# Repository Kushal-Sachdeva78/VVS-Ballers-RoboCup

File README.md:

<h1 align="center">VVS Ballers: RoboCupJunior Soccer</h1>

<p align="center">
  Autonomous RoboCupJunior Soccer robots by Team VVS Ballers, designed and iterated
  across multiple seasons, from EV3 regional robots to a custom Teensy-based
  international platform.<br>
  Firmware (C++) · multi-board electronics (KiCad) · mechanical design (Fusion 360).<br>
  For RoboCupJunior teams building their own robots.
</p>

```bash
git clone https://github.com/Kushal-Sachdeva78/VVS-Ballers-RoboCup
```
<!-- DEMO: cut a 5-10 s GIF from "RoboCup Nationals 2025-26/Gallery/Finals Video.mp4", save as docs/demo.gif, then replace this line with  -->

---

## Results

- **RoboCup 2026, Incheon, South Korea (International): 9th place, RoboCupJunior Soccer (IR League).** Two self-built robots, designed, wired, and programmed by a team of two.
- **RoboCupJunior India, 2025-26 season**: came up through the Indian regional and national rounds to qualify for RoboCup 2026. The trophy and finals footage from the national event are in the [Nationals gallery](RoboCup%20Nationals%202025-26/Gallery).

## Press and media

- [Two Students, Two Self-Built Robots, And A 9th-Place Finish At The Robot "World Cup"](https://www.republicworld.com/sports/two-students-two-self-built-robots-and-a-ninth-place-finish-at-the-robot-world-cup-2026-07-14-132303) (Republic World, July 2026)
- [Team Instagram](https://www.instagram.com/vvs_ballers) - Robot builds, competition footage, and event coverage

---

## Seasons

| Season | What's inside |
|---|---|
| **[RoboCup Internationals 2025-26](RoboCup%20Internationals%202025-26/)** ⭐ *current* | Two autonomous Soccer-Infrared robots (attacker + defender): a Teensy 4.1 multi-board stack with an IR ball ring, line ring, ultrasonic, OpenMV goal camera, and 48 V solenoid kicker. Firmware + KiCad PCBs + Fusion CAD. |
| **[RoboCup Nationals 2025-26](RoboCup%20Nationals%202025-26/)** | Nationals build: EV3 robot program (HiTechnic IR seeker and compass), an Arduino relay-driven solenoid kicker, 3D-printed chassis parts, the season poster, and the trophy and finals gallery. |
| **[RoboCup Regionals 2025-26](RoboCup%20Regionals%202025-26/)** | EV3 holonomic robot (diamond omni drive, dual underside colour sensors, side IR distance, IR seeker, compass heading hold) + an Arduino ultrasonic-triggered kicker + printable parts + poster. |
| **[RoboCup 2024-25](RoboCup%202024-25/)** | Prior season: international Team Description Paper, posters, and earlier EV3 reference designs. |

> The **Internationals 2025-26** robots are the current flagship, and the rest of this
> page focuses on them. The full detail lives in that folder's
> **[detailed README](RoboCup%20Internationals%202025-26/README.md)** and a complete
> **[technical deep-dive](RoboCup%20Internationals%202025-26/Docs/HOW_IT_WORKS.md)**.
> Competition media: **[TDP](RoboCup%20Internationals%202025-26/Docs/TDP.md)** ·
> **[poster](RoboCup%20Internationals%202025-26/Docs/RoboCup_Internationals_Poster.png)** ·
> **[TDP video](https://github.com/Kushal-Sachdeva78/VVS-Ballers-RoboCup/releases/download/internationals-2025-26-media/VVS_Ballers_TDP_Video.mp4)** ·
> **[photo gallery](RoboCup%20Internationals%202025-26/Docs/Images)**.
>
> Code-span paths below (e.g. `Firmware/Attacker`) are relative to
> [`RoboCup Internationals 2025-26/`](RoboCup%20Internationals%202025-26/).

### Earlier-season highlights

- **Regionals 2025-26 (EV3):** EV3 motors driving omni wheels in a **diamond** layout;
  underside colour sensors for white-line and goal-area avoidance; side IR sensors for
  walls; an IR seeker for ball tracking; and a compass for heading correction. An
  external Arduino kicker (TB6612FNG H-bridge + gearmotor, ultrasonic ball detect)
  steps through kick, hold, retract, and cooldown phases.
- **Nationals 2025-26 (EV3):** the same EV3 sensing platform, upgraded with a
  relay-driven solenoid kicker triggered by an ultrasonic capture sensor. The custom
  Teensy and KiCad electronics stack was developed next, for the Internationals robots.

---

## Internationals 2025-26: the robots at a glance

Both robots share one electronics stack and one chassis; only the role firmware on
the main board differs.

| | Attacker | Defender (goalkeeper) |
|---|---|---|
| Job | Win the ball, aim, and shoot the open corner | Hold the goal mouth and clear the ball |
| Main firmware | `Firmware/Attacker/Attacker_Chase_Aim_Kick_Line` | `Firmware/Defender/Defender_Full` |
| Ball | IR ring (16 sensors) | IR ring |
| Staying in bounds | **Line ring + ultrasonic fused** boundary escape | **Line** keeps it on the goal-area ("D") line; ultrasonic cross-check |
| Goal / aim | OpenMV camera to open-corner bearing | (camera optional) |
| Kicker | 48 V solenoid, camera-gated | Short clearing kick |

## Electronics: the boards

A **multi-board design**: each subsystem has its own microcontroller, and the boards
talk to the main board over compact **UART links** (CRC-8-framed, bar the plain-ASCII
IR link), keeping the fast sensor loops off the main control CPU.

| Board | MCU | Does | KiCad | Firmware |
|---|---|---|---|---|
| **Main** | Teensy 4.1 | Drive (4x DRV8263H), BNO055 IMU, capture sensor, kicker relay, all links | `PCB/Main` | `Firmware/Attacker`, `Firmware/Defender` |
| **IR ring** | Teensy 4.1 | 16x TSSP58038 for ball bearing and distance | `PCB/IR` | `Firmware/IR_Ball_Sensor` |
| **Line ring** | Teensy 4.1 | 4x QTR-MD-05A (18 ch) for white-line detection | `PCB/Line` | `Firmware/Line_Sensor` |
| **Ultrasonic** | Arduino Nano Every | 4x HC-SR04 for wall distances | `PCB/Ultrasonic` | `Firmware/Ultrasonic` |
| **Camera** | OpenMV H7 | Goal / keeper / open-corner vision | - | `Firmware/Camera` |
| **Power** | - | 12 V / 5 V / 3.3 V rails + 48 V solenoid boost | `PCB/Power` | - |
| **Motor-current** (optional) | Arduino Nano Every | DRV8263H stall / over-current watchdog | - | `Firmware/Motor_Current` |

Human-readable wiring PDFs for the Main, Power, IR, and Line boards are in
**[`PCB/Wiring/`](RoboCup%20Internationals%202025-26/PCB/Wiring)**.

## How it plays: design choices vs. the game

Everything is built around what actually wins (and loses) a RoboCupJunior Soccer
match. (A goal counts when the ball touches the **back wall of the goal**; touching a
wall or driving fully into the marked penalty area is an **out-of-bounds penalty**.)

- **Score in the goal.** The IR ring gives the ball's bearing; the main board chases
  it with an omni-wheel drive held straight by a BNO055 heading PID. Once the ball is
  captured, the OpenMV camera finds the goal, picks the **open corner** (dodging the
  keeper), and the chassis turns in place until that corner is dead ahead before the
  solenoid fires. Aiming for the open corner instead of the goal centre is how you
  beat a keeper.

- **Never cross the line (the expensive mistake).** The attacker treats a side as the
  field boundary **only when the line ring and the ultrasonics agree** (white line
  seen *and* wall within 300 mm), then flees away from it. Two independent sensors
  must concur, so one noisy reading can't make the robot dart out of bounds.

- **Keep the keeper on its line, not inside the box.** No robot may be *fully* inside
  the penalty area, so the defender uses the line ring to ride the **edge of the goal
  area ("the D")** while tracking the ball laterally and clearing it on contact.

- **Stay legal in the Infrared league.** IR-emitting rangefinders (ToF, LiDAR, IR
  distance sensors) are **banned** because they'd swamp other robots' IR ball
  sensors. That is why walls are ranged with **ultrasonic** HC-SR04s here, not IR.

- **Power within the rules.** The rules cap robot power at **48 V DC**; the solenoid
  kicker runs from a 48 V boost converter (right at the legal ceiling, for the hardest
  legal kick) while logic and motors run from 3.3 V / 5 V / 12 V rails.

- **Referee start/stop.** The main board pins out the RoboCupJunior **Communication
  Module** GO/STOP inputs, with firmware support toggled via `USE_COMMS` in the
  defender build.

The binary inter-board links (ultrasonic, line, camera to main) are short frames, each
guarded by an identical **CRC-8 (poly 0x07)**; the IR link is plain delimited ASCII.
Full byte-level layouts are in the
[technical deep-dive](RoboCup%20Internationals%202025-26/Docs/HOW_IT_WORKS.md).

## Team

| Member | Roles |
|---|---|
| **Kushal Sachdeva** (Team Leader) | Electrical, Software & CAD |
| **Darsh Goel** | Mechanical & CAD |

Region: **India** · League: **RoboCupJunior Soccer Infrared**

## Sponsors

Our thanks to **Amazon · DLF · Havells · OpenMV · Magnum Ventures · Budtree
Management**, and to our mentors, school, and the RoboCup Junior community for their
support.

## Related projects

- [K.A.D-Ballers-Genius-Olympiad](https://github.com/Kushal-Sachdeva78/K.A.D-Ballers-Genius-Olympiad): our mecanum-drive robot for the GENIUS Olympiad robotics competition
- More at [github.com/Kushal-Sachdeva78](https://github.com/Kushal-Sachdeva78)

## License

Released under the **MIT License**; see [`LICENSE`](LICENSE).
© 2026 VVS Ballers (Kushal Sachdeva, Darsh Goel). You're welcome to learn from and
build on this work; please keep the attribution.

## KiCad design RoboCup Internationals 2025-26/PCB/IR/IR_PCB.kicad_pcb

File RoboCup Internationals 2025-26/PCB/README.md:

# PCB

KiCad sources, Gerbers, drill and job files for every board, plus human-readable
wiring and ready-to-order fab packages.

| Folder | Board | Contents |
|---|---|---|
| `Main/` | Main board (Teensy 4.1 carrier) | KiCad source + Gerbers — drivers, IMU, links, kicker relay (Main_PCB 2.0) |
| `IR/` | IR ball ring | 16× TSSP58038 + Teensy |
| `Line/` | Line ring | 4× QTR-MD-05A + Teensy |
| `Ultrasonic/` | Ultrasonic board | 4× HC-SR04 + Nano Every |
| `Power/` | Power board | 12 V / 5 V / 3.3 V rails + 48 V solenoid boost |
| `Wiring/` | — | **one wiring PDF per board** (the netlist in plain language) |
| `Fabrication/` | — | ready-to-order Gerber **zips** |

The previous main board revision is archived in
[`../Legacy/PCB/Main_v1`](../Legacy/PCB/Main_v1).

## Opening the sources

Each board folder is a KiCad project — open the `*.kicad_pro` (the matching
`.kicad_pcb` and `.kicad_sch` sit beside it). The loose `*.gbr` / `*.drl` /
`*.gbrjob` files are **generated** fabrication outputs; for ordering, prefer the
zipped packages in [`Fabrication/`](Fabrication). KiCad local-settings files
(`*.kicad_prl`) and auto-backups are intentionally git-ignored.

## Start with the wiring PDFs

If you only read one thing, read [`Wiring/`](Wiring): `Main_PCB.pdf`, `Power_PCB.pdf`,
`IR_PCB.pdf`, and `Line_PCB.pdf` list every connection (rails, sensor pins, UART
links) in plain language. They are the reference the firmware pin maps were verified
against.

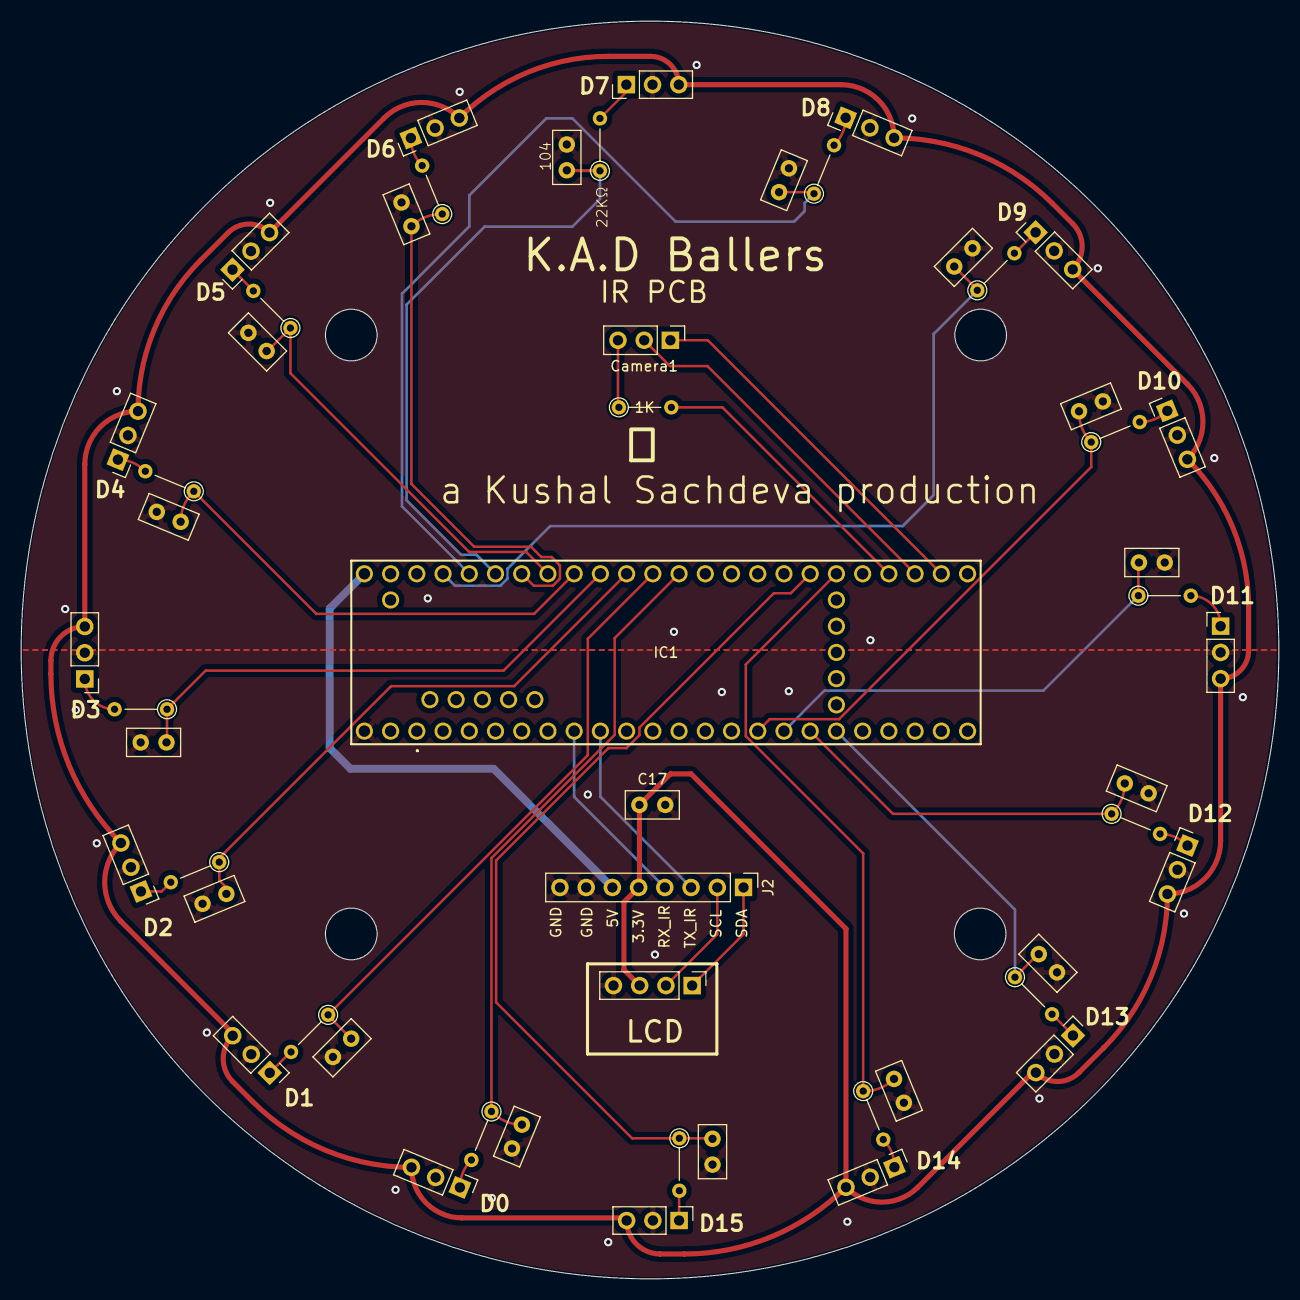
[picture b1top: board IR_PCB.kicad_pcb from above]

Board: 2 copper layers, 121.8 x 121.8 mm, 54 parts (0 on the bottom side), 43 nets.

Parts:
1K: 1K; R_Axial_DIN0204_L3.6mm_D1.6mm_P5.08mm_Vertical
C1, C2, C3, C4, C5, C6, C7, C8, C9, C10, C11, C12, C13, C14, C15, C16: 104; C_Disc_D5.0mm_W2.5mm_P2.50mm
C17: C; C_Disc_D5.0mm_W2.5mm_P2.50mm
Camera1: Conn_01x03; PinHeader_1x03_P2.54mm_Vertical
IC1: TEENSY_4.1; TEENSY41
J1: Conn_01x04_Socket; PinHeader_1x04_P2.54mm_Vertical
J2: Conn_01x08; PinHeader_1x08_P2.54mm_Vertical
R1, R2, R3, R4, R5, R6, R7, R8, R9, R10, R11, R12, R13, R14, R15, R16: 22k; R_Axial_DIN0204_L3.6mm_D1.6mm_P5.08mm_Vertical
U2, U3, U4, U5, U6, U7, U8, U9, U10, U11, U12, U13, U14, U15, U16, U17: TSSP58038; PinHeader_1x03_P2.54mm_Vertical

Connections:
+3.3V: C17.1, J1.3, J2.5, U2.3 (Vin), U3.3 (Vin), U4.3 (Vin), U5.3 (Vin), U6.3 (Vin), U7.3 (Vin), U8.3 (Vin), U9.3 (Vin), U10.3 (Vin), U11.3 (Vin), U12.3 (Vin), U13.3 (Vin), U14.3 (Vin), U15.3 (Vin), U16.3 (Vin), U17.3 (Vin)
+5V: IC1.55 (VIN_(3.6_TO_5.5_VOLTS)), J2.6
D0: C3.1, IC1.14 (A0), R3.1
D1: C4.1, IC1.15 (A1), R4.1
D2: C1.1, IC1.16 (A2), R1.1
D3: C2.1, IC1.17 (A3), R2.1
D4: C5.1, IC1.18 (A4), R5.1
D5: C6.1, IC1.19 (A5), R6.1
D6: C7.1, IC1.20 (A6), R7.1
D7: C8.1, IC1.21 (A7), R8.1
D8: C11.1, IC1.22 (A8), R11.1
D9: C12.1, IC1.23 (A9), R12.1
D10: C9.1, IC1.24 (A10), R9.1
D11: C10.1, IC1.25 (A11), R10.1
D12: C13.1, IC1.26 (A12), R13.1
D13: C14.1, IC1.27 (A13), R14.1
D14: C15.1, IC1.38 (A14), R15.1
D15: C16.1, IC1.39 (A15), R16.1
GND: C1.2, C2.2, C3.2, C4.2, C5.2, C6.2, C7.2, C8.2, C9.2, C10.2, C11.2, C12.2, C13.2, C14.2, C15.2, C16.2, C17.2, IC1.71 (GND_6), J1.4, J2.7, J2.8, U2.2 (GND), U3.2 (GND), U4.2 (GND), U5.2 (GND), U6.2 (GND), U7.2 (GND), U8.2 (GND), U9.2 (GND), U10.2 (GND), U11.2 (GND), U12.2 (GND), U13.2 (GND), U14.2 (GND), U15.2 (GND), U16.2 (GND), U17.2 (GND)
IRout0: R3.2, U2.1 (OUT)
IRout1: R4.2, U3.1 (OUT)
IRout2: R1.2, U4.1 (OUT)
IRout3: R2.2, U5.1 (OUT)
IRout4: R5.2, U6.1 (OUT)
IRout5: R6.2, U7.1 (OUT)
IRout6: R7.2, U8.1 (OUT)
IRout7: R8.2, U9.1 (OUT)
IRout8: R11.2, U10.1 (OUT)
IRout9: R12.2, U11.1 (OUT)
IRout10: R9.2, U12.1 (OUT)
IRout11: R10.2, U13.1 (OUT)
IRout12: R13.2, U14.1 (OUT)
IRout13: R14.2, U15.1 (OUT)
IRout14: R15.2, U16.1 (OUT)
IRout15: R16.2, U17.1 (OUT)
unnamed: 1K.1, Camera1.3
RST_C: 1K.2, IC1.36 (CS_2)
RX_Ball: IC1.7 (RX2), J2.4
RX_C: Camera1.2, IC1.35 (TX8)
SCL_LCD: J1.2, J2.2
SDA_LCD: J1.1, J2.1
TX_Ball: IC1.8 (TX2), J2.3
TX_C: Camera1.1, IC1.34 (RX8)

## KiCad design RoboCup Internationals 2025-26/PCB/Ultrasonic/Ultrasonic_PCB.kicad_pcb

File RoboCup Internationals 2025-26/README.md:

<h1 align="center">VVS Ballers — RoboCupJunior Soccer (Internationals 2025-26)</h1>

<p align="center">
  Two fully autonomous robots — an <b>attacker</b> and a <b>defender</b> — for the
  <b>RoboCupJunior Soccer Infrared</b> (formerly Lightweight) league.<br>
  Firmware(C++) · multi-board electronics (KiCad) · mechanical design (Fusion 360).
</p>

---

## About

This folder is the **Internationals 2025-26** season of the VVS Ballers
RoboCupJunior Soccer robots — the firmware that runs them, the PCBs that make up
their electronics, and the CAD for their chassis. The robots chase an infrared-emitting ball, find the goal with a
camera, kick with a solenoid, and stay inside the field using a line-sensor ring
backed up by ultrasonic ranging.

In **RoboCupJunior Soccer**, two teams of two robots play autonomous soccer on a
green field with white boundary lines. A goal is scored when the ball touches the
**back wall of the goal**; touching a wall or driving fully into the marked
penalty area is an **out-of-bounds penalty**. Every design decision here
is made against those facts — score in the goal, never cross the line, stay legal.
(See [How the robot works](Docs/HOW_IT_WORKS.md) for the full technical write-up.)

> **2026 ball note:** the Soccer Infrared league switched to the new 42 mm
> open-source [IR golf ball](https://github.com/robocup-junior/ir-golf-ball) — the
> same size as the Vision-league golf ball. The IR ring firmware here is tuned for it.

## Competition documents & media

| | |
|---|---|
| 📄 **Team Description Paper** | [`Docs/TDP.md`](Docs/TDP.md) |
| 🎬 **TDP video** | [Watch / download](https://github.com/Kushal-Sachdeva78/VVS-Ballers-RoboCup/releases/download/internationals-2025-26-media/VVS_Ballers_TDP_Video.mp4) (154 MB, hosted under [Releases](https://github.com/Kushal-Sachdeva78/VVS-Ballers-RoboCup/releases)) |
| 🖼️ **Poster** | [`Docs/RoboCup_Internationals_Poster.png`](Docs/RoboCup_Internationals_Poster.png) |
| 🎤 **Group-interview deck** | [`Docs/VVS_Ballers_GroupInterview_Deck.pptx`](Docs/VVS_Ballers_GroupInterview_Deck.pptx) |
| 📊 **Block diagram & BOM** | [`Docs/VVS_Ballers_Electronics_Block_Diagram.png`](Docs/VVS_Ballers_Electronics_Block_Diagram.png) · [`Docs/VVS_Ballers_BOM.xlsx`](Docs/VVS_Ballers_BOM.xlsx) |
| 📷 **Photo gallery** | [`Docs/Images/`](Docs/Images) — robots · electronics · mechanical · diagrams · team |

<p align="center">
  
</p>

## Team

| Member | Roles |
|---|---|
| **Kushal Sachdeva** (Team Leader) | Electrical, Software & CAD |
| **Darsh Goel** | Mechanical & CAD |

Region: **India** · League: **RoboCupJunior Soccer Infrared**

## The robots at a glance

Both robots share one electronics stack and one chassis; only the role firmware on
the main board differs.

| | Attacker | Defender (goalkeeper) |
|---|---|---|
| Job | Win the ball, aim, and shoot the open corner | Hold the goal mouth and clear the ball |
| Main firmware | `Firmware/Attacker/Attacker_Chase_Aim_Kick_Line` | `Firmware/Defender/Defender_Full` |
| Ball | IR ring (16 sensors) | IR ring |
| Staying in bounds | **Line ring + ultrasonic fused** boundary escape | **Line** keeps it on the goal-area ("D") line; ultrasonic cross-check |
| Goal / aim | OpenMV camera → open-corner bearing | (camera optional) |
| Kicker | 48 V solenoid, camera-gated | Short clearing kick |

## Electronics — the boards

The robot is a **multi-board design**: each subsystem has its own microcontroller,
and the boards talk to the main board over compact **UART links** (CRC-8-framed, bar
the plain-ASCII IR link). This keeps
the fast sensor loops off the main control CPU.

| Board | MCU | Does | KiCad | Firmware |
|---|---|---|---|---|
| **Main** | Teensy 4.1 | Drive (4× DRV8263H), BNO055 IMU, capture sensor, kicker relay, all links | `PCB/Main` | `Firmware/Attacker`, `Firmware/Defender` |
| **IR ring** | Teensy 4.1 | 16× TSSP58038 → ball bearing & distance | `PCB/IR` | `Firmware/IR_Ball_Sensor` |
| **Line ring** | Teensy 4.1 | 4× QTR-MD-05A (18 ch) → white-line detection | `PCB/Line` | `Firmware/Line_Sensor` |
| **Ultrasonic** | Arduino Nano Every | 4× HC-SR04 → wall distances | `PCB/Ultrasonic` | `Firmware/Ultrasonic` |
| **Camera** | OpenMV H7 | Goal / keeper / open-corner vision | — | `Firmware/Camera` |
| **Power** | — | 12 V / 5 V / 3.3 V rails + 48 V solenoid boost | `PCB/Power` | — |
| **Motor-current** (optional) | Arduino Nano Every | DRV8263H stall / over-current watchdog | — | `Firmware/Motor_Current` |

Wiring for every board is in **[`PCB/Wiring/`](PCB/Wiring)** (one PDF per board) and
explained in [How the robot works](Docs/HOW_IT_WORKS.md). A whole-robot
[electronics block diagram](Docs/VVS_Ballers_Electronics_Block_Diagram.png) and the
full [bill of materials](Docs/VVS_Ballers_BOM.xlsx) live in `Docs/`.

<p align="center"><i>The five boards — Main 2.0 · IR ring · Line ring · Power · Ultrasonic
(KiCad renders; build photos in <a href="Docs/Images/Electronics">Docs/Images/Electronics</a>)</i></p>

## How it plays — design choices vs. the game

Everything here is built around what actually wins (and loses) a RoboCupJunior
Soccer match:

- **Score in the goal.** The IR ring gives the ball's bearing; the main board chases
  it with an omni-wheel drive held straight by a BNO055 heading PID. Once the ball
  is captured, the OpenMV camera finds the goal, picks the **open corner** (dodging
  the keeper), and the chassis turns in place until that corner is dead ahead before
  the solenoid fires. Aiming the open corner instead of the goal centre is how you
  beat a keeper.

- **Never cross the line (the expensive mistake).** Touching a wall *or* driving
  fully into the marked penalty area is an **out-of-bounds penalty** — the robot is
  removed for a minute, and any goal scored while it's penalised is wiped. The
  attacker therefore treats a side as the field boundary **only when the line ring
  and the ultrasonics agree** (white line seen *and* wall within 300 mm), then flees
  away from it. Two independent sensors must concur, so one noisy reading can't make
  the robot dart out of bounds.

- **Keep the keeper on its line, not inside the box.** No robot may be *fully* inside
  the penalty area (that's out of bounds), so the defender uses the line ring to ride
  the **edge of the goal area ("the D")** — staying on the line rather than crossing
  it — while tracking the ball laterally and clearing it on contact.

- **Stay legal in the Infrared league.** IR-emitting rangefinders (ToF, LiDAR, IR
  distance sensors) are **banned** in the Infrared league because they'd swamp other
  robots' IR ball sensors — which is exactly why walls are ranged with **ultrasonic**
  HC-SR04s here, not IR. The reflectance line sensors face **down at the floor** and
  are shrouded so their light can't be mistaken for the orange ball by other teams'
  cameras.

- **Power within the rules.** The rules cap robot power at **48 V DC**; the solenoid
  kicker runs from a 48 V boost converter — right at the legal ceiling for the
  hardest legal kick — while logic and motors run from 3.3 V / 5 V / 12 V rails.

- **Referee start/stop.** The main board reads the RoboCupJunior **Communication
  Module** GO/STOP lines, so a referee can start and halt the robot as the rules
  require at the international competition.

## Folder structure

```
RoboCup Internationals 2025-26/
├─ README.md                  ← you are here
├─ Docs/
│  ├─ HOW_IT_WORKS.md         ← full technical deep-dive
│  ├─ MAPPING.md              ← original → new file/folder mapping
│  ├─ TDP.md                  ← Team Description Paper (Markdown)
│  ├─ TDP_images/             ← images embedded in TDP.md
│  ├─ RoboCup_Internationals_Poster.png
│  ├─ VVS_Ballers_GroupInterview_Deck.pptx
│  ├─ VVS_Ballers_BOM.xlsx    ← bill of materials
│  ├─ VVS_Ballers_Electronics_Block_Diagram.png
│  └─ Images/                 ← gallery: Robots · Electronics · Mechanical · Diagrams · Team
├─ Firmware/                  ← all microcontroller code
│  ├─ Attacker/               ← main-board attacker (current: …_Line)
│  ├─ Defender/               ← main-board goalkeeper (Defender_Full)
│  ├─ IR_Ball_Sensor/         ← IR ring (Code2_Calibrated = flight build)
│  ├─ Line_Sensor/            ← QTR line ring (Detect / Baseline / Raw)
│  ├─ Ultrasonic/             ← Nano Every HC-SR04 board + main-board parser
│  ├─ Camera/                 ← OpenMV H7 goal vision (MicroPython)
│  ├─ Motor_Current/          ← optional over-current watchdog
│  └─ README.md
├─ PCB/                       ← KiCad sources, Gerbers, wiring PDFs, fab zips
│  ├─ Main/ IR/ Line/ Ultrasonic/ Power/
│  ├─ Wiring/        ← human-readable wiring per board (PDF)
│  ├─ Fabrication/   ← ready-to-order Gerber zips
│  └─ README.md
├─ CAD/                       ← Fusion 360 sources + printable STLs
│  ├─ Fusion/   Printable/{Chassis, Drive, Ball_Capture, Sensor_Mounts}
│  └─ README.md
└─ Legacy/                    ← superseded designs, kept for history (see Legacy/README.md)
```

## Build & flash

All boards build in the **Arduino IDE** (each sketch folder is named to match its
`.ino`); the Teensy/Nano sketches also build under **PlatformIO** via the
`platformio.ini` in each folder.

| Target | Board setting | Libraries / notes |
|---|---|---|
| Main board (attacker/defender) | Teensy 4.1, USB Type *Serial* | Adafruit BNO055 + Adafruit Unified Sensor (Defender OLED option also needs SSD1306 + GFX) |
| IR ring | Teensy 4.1 | none (core `analogRead`) — flash `Code2_Calibrated` |
| Line ring | Teensy 4.1 | none |
| Ultrasonic | Arduino Nano Every (megaAVR) | none; *Registers emulation → None (ATMEGA4809)* |
| Motor-current | Arduino Nano Every | none |
| Camera | OpenMV H7 | save `Goal_Cam.py` to the H7 flash as `main.py` |

PlatformIO example: `pio run -e teensy41 -t upload` (Teensy) or
`pio run -e nano_every -t upload` (Nano).

## Inter-board links (summary)

Three of the four links are short binary frames with a 2-byte sync and an identical
**CRC-8 (poly 0x07)**, so the main board can reject any corrupted frame; the IR link
is plain delimited ASCII:

- **IR → Main** (Serial4): ASCII `"<dir>a … <dist>b"`, `500` = no ball (no checksum).
- **Ultrasonic → Main** (Serial3): 13-byte frame, four `uint16` mm distances + status.
- **Line → Main** (Serial8): 9-byte frame, per-side white-line bitmask + counts.
- **Camera → Main** (Serial2): 11-byte frame, goal/keeper/ball flags + bearings,
  open-corner angle, and the orange-ball bearing/distance (camera+IR fusion).

Full byte-level layouts are in [How the robot works](Docs/HOW_IT_WORKS.md).

## Sponsors

Our thanks to **Amazon · DLF · Havells · OpenMV · Magnum Ventures · Budtree
Management** for supporting the team.

## License

Released under the [MIT License](LICENSE) © 2026 VVS Ballers. You're welcome to
learn from and build on this work — please keep the attribution.

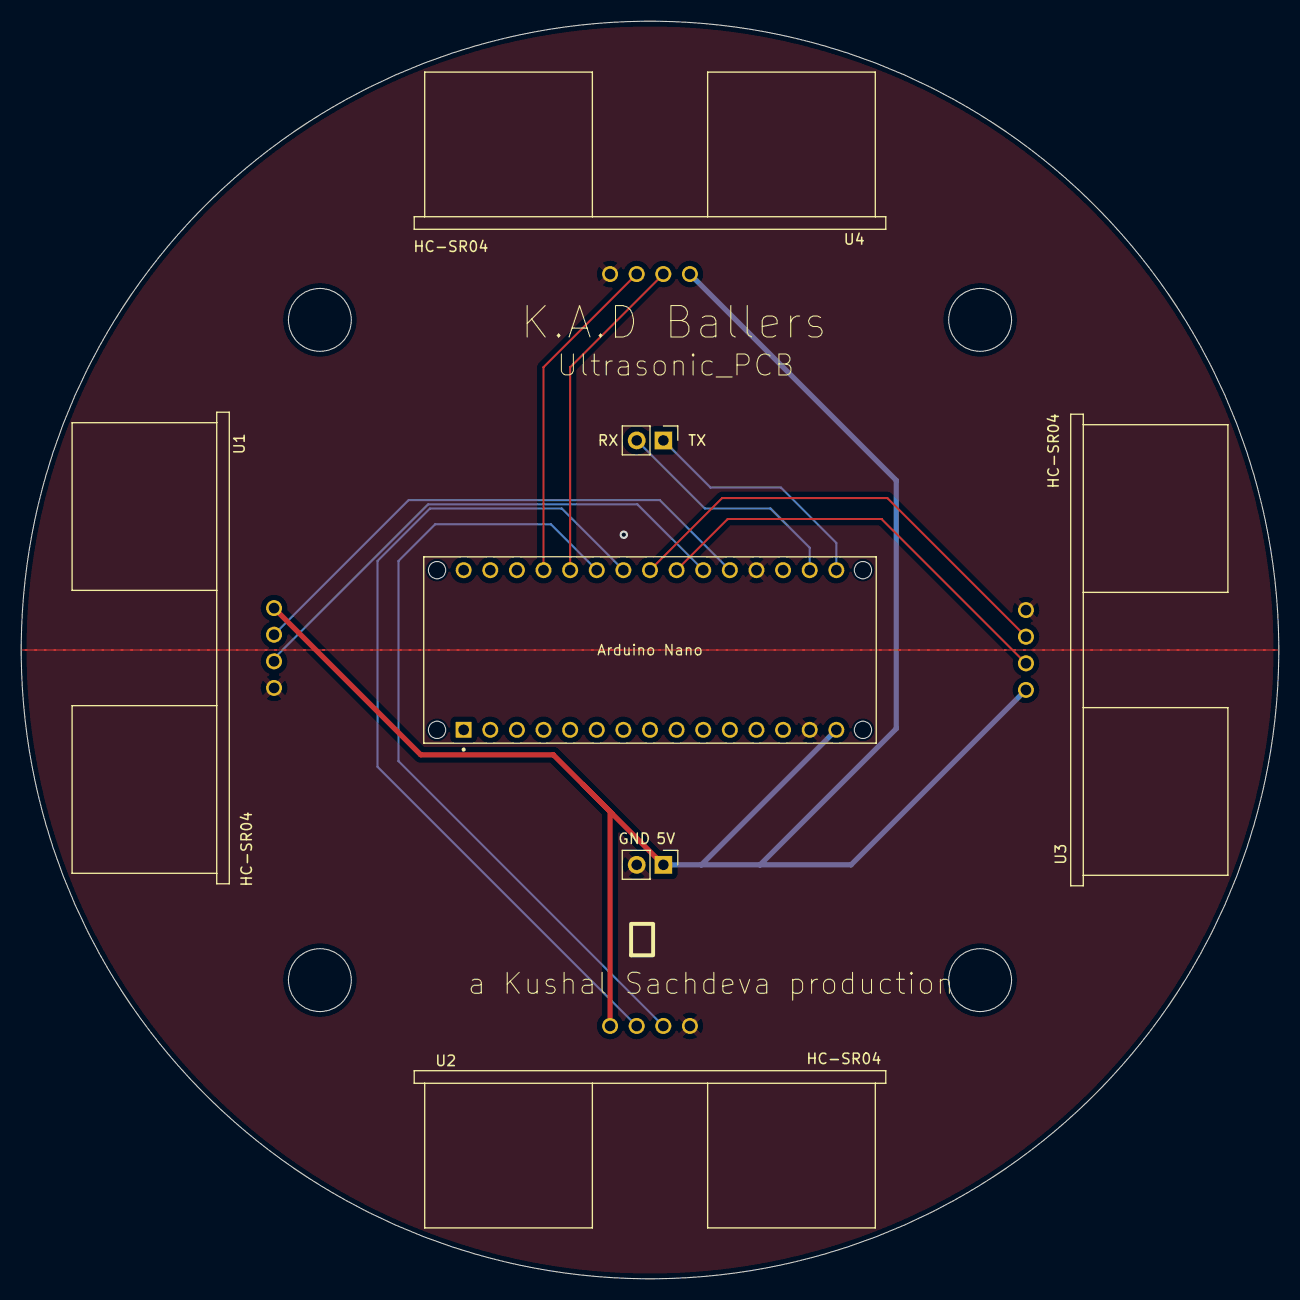
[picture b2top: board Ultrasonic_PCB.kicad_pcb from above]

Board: 2 copper layers, 120.0 x 120.0 mm, 7 parts (0 on the bottom side), 12 nets.

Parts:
5V: Conn_01x02; PinHeader_1x02_P2.54mm_Vertical
Arduino Nano: ABX00028; MODULE_ABX00028
RX: Conn_01x02; PinHeader_1x02_P2.54mm_Vertical
U1, U2, U3, U4: HC-SR04; XCVR_HC-SR04

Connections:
GND: 5V.2, Arduino Nano.14 (GND), Arduino Nano.19 (GND), U1.4 (GND), U2.4 (GND), U3.4 (GND), U4.4 (GND)
unnamed: 5V.1, Arduino Nano.15 (VIN), U1.1 (VCC), U2.1 (VCC), U3.1 (VCC), U4.1 (VCC)
unnamed: Arduino Nano.16 (TX), RX.1
unnamed: Arduino Nano.17 (RX), RX.2
unnamed: Arduino Nano.20 (D2), U1.2 (TRIG)
unnamed: Arduino Nano.21 (D3/PWM), U1.3 (ECHO)
unnamed: Arduino Nano.22 (D4), U3.2 (TRIG)
unnamed: Arduino Nano.23 (D5/PWM), U3.3 (ECHO)
unnamed: Arduino Nano.24 (D6/PWM), U2.2 (TRIG)
unnamed: Arduino Nano.25 (D7), U2.3 (ECHO)
unnamed: Arduino Nano.26 (D8), U4.2 (TRIG)
unnamed: Arduino Nano.27 (D9/PWM), U4.3 (ECHO)

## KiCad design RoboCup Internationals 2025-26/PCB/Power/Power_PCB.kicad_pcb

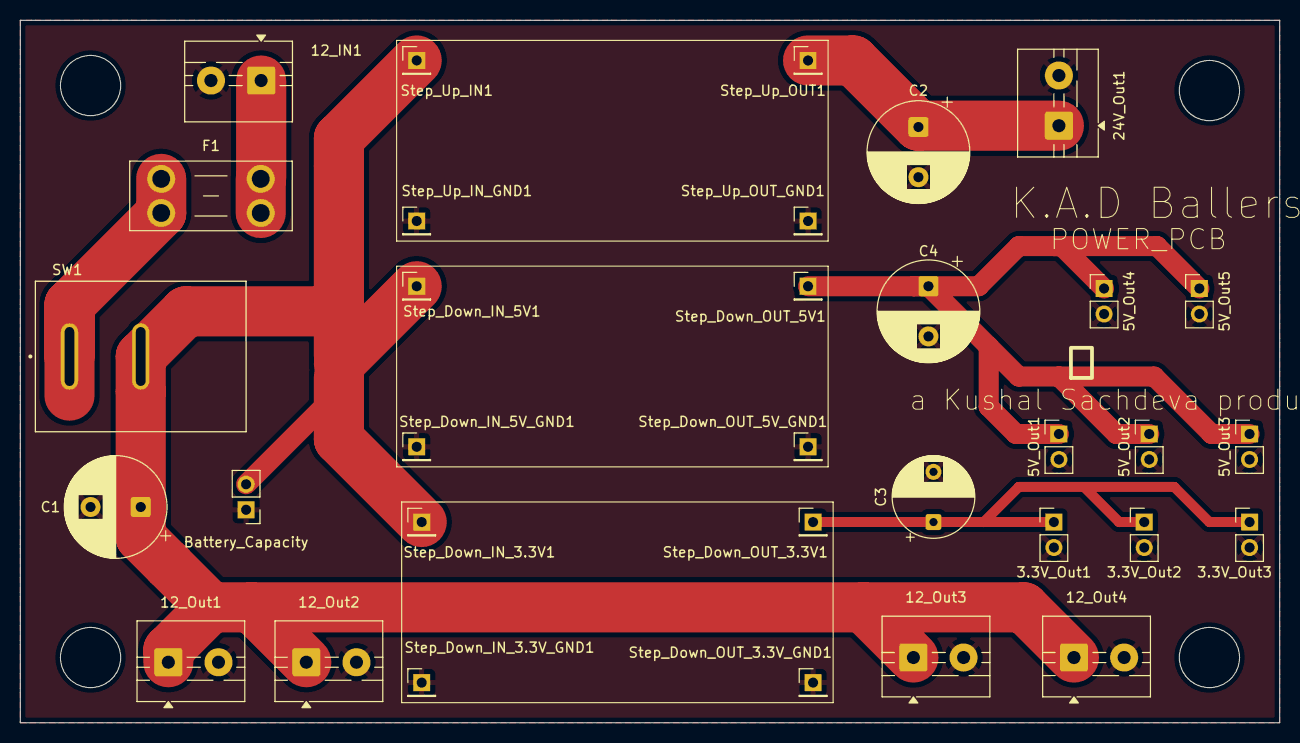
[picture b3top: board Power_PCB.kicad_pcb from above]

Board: 2 copper layers, 125.5 x 70.0 mm, 33 parts (0 on the bottom side), 7 nets.

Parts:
3.3V_Out1, 3.3V_Out2, 3.3V_Out3: Conn_01x02; PinHeader_1x02_P2.54mm_Vertical
5V_Out1: IR; PinHeader_1x02_P2.54mm_Vertical
5V_Out2: Line; PinHeader_1x02_P2.54mm_Vertical
5V_Out3: Main_PCB; PinHeader_1x02_P2.54mm_Vertical
5V_Out4: US_PCB; PinHeader_1x02_P2.54mm_Vertical
5V_Out5: Camera; PinHeader_1x02_P2.54mm_Vertical
12_IN1, 12_Out1, 12_Out2, 12_Out3, 12_Out4: Screw_Terminal_01x02; TerminalBlock_MaiXu_MX126-5.0-02P_1x02_P5.00mm
24V_Out1: Conn_01x02; TerminalBlock_MaiXu_MX126-5.0-02P_1x02_P5.00mm
Battery_Capacity: Conn_01x02; PinHeader_1x02_P2.54mm_Vertical
C1, C2, C4: C; CP_Radial_D10.0mm_P5.00mm
C3: C; CP_Radial_D8.0mm_P5.00mm
F1: Fuse; Fuseholder_Blade_Mini_Keystone_3568
SW1: SW_DIP_x01; SW_RF1-1A-DC-2-R-1
Step_Down_IN_3.3V1, Step_Down_IN_3.3V_GND1, Step_Down_IN_5V1, Step_Down_IN_5V_GND1: Conn_01x01; PinHeader_1x01_P2.54mm_Vertical
Step_Down_OUT_3.3V1, Step_Down_OUT_3.3V_GND1, Step_Down_OUT_5V1, Step_Down_OUT_5V_GND1: Conn_01x01; PinHeader_1x01_P2.54mm_Vertical
Step_Up_IN1: Conn_01x01; PinHeader_1x01_P2.54mm_Vertical
Step_Up_IN_GND1: Conn_01x01; PinHeader_1x01_P2.54mm_Vertical
Step_Up_OUT1: Conn_01x01; PinHeader_1x01_P2.54mm_Vertical
Step_Up_OUT_GND1: Conn_01x01; PinHeader_1x01_P2.54mm_Vertical

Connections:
GND: 3.3V_Out1.2, 3.3V_Out2.2, 3.3V_Out3.2, 5V_Out1.2, 5V_Out2.2, 5V_Out3.2, 5V_Out4.2, 5V_Out5.2, 12_IN1.2, 12_Out1.2, 12_Out2.2, 12_Out3.2, 12_Out4.2, 24V_Out1.2, Battery_Capacity.1, C1.2, C2.2, C3.2, C4.2, Step_Down_IN_3.3V_GND1.1, Step_Down_IN_5V_GND1.1, Step_Down_OUT_3.3V_GND1.1, Step_Down_OUT_5V_GND1.1, Step_Up_IN_GND1.1, Step_Up_OUT_GND1.1
unnamed: 3.3V_Out1.1, 3.3V_Out2.1, 3.3V_Out3.1, C3.1, Step_Down_OUT_3.3V1.1
unnamed: 5V_Out1.1, 5V_Out2.1, 5V_Out3.1, 5V_Out4.1, 5V_Out5.1, C4.1, Step_Down_OUT_5V1.1
unnamed: 12_IN1.1, F1.2
unnamed: 12_Out1.1, 12_Out2.1, 12_Out3.1, 12_Out4.1, Battery_Capacity.2, C1.1, SW1.2, Step_Down_IN_3.3V1.1, Step_Down_IN_5V1.1, Step_Up_IN1.1
unnamed: 24V_Out1.1, C2.1, Step_Up_OUT1.1
unnamed: F1.1, SW1.1

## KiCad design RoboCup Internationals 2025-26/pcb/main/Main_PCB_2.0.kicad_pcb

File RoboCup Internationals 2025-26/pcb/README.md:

# PCB

KiCad sources, Gerbers, drill and job files for every board, plus human-readable
wiring and ready-to-order fab packages.

| Folder | Board | Contents |
|---|---|---|
| `main/` | Main board (Teensy 4.1 carrier) | KiCad source + Gerbers — drivers, IMU, links, kicker relay (Main_PCB 2.0) |
| `ir/` | IR ball ring | 16× TSSP58038 + Teensy |
| `line/` | Line ring | 4× QTR-MD-05A + Teensy |
| `ultrasonic/` | Ultrasonic board | 4× HC-SR04 + Nano Every |
| `power/` | Power board | 12 V / 5 V / 3.3 V rails + 48 V solenoid boost |
| `wiring/` | — | **one wiring PDF per board** (the netlist in plain language) |
| `fab/` | — | ready-to-order Gerber **zips** |

The previous main board revision is archived in
[`../legacy/pcb/main-v1`](../legacy/pcb/main-v1).

## Opening the sources

Each board folder is a KiCad project — open the `*.kicad_pro` (the matching
`.kicad_pcb` and `.kicad_sch` sit beside it). The loose `*.gbr` / `*.drl` /
`*.gbrjob` files are **generated** fabrication outputs; for ordering, prefer the
zipped packages in [`fab/`](fab). KiCad local-settings files (`*.kicad_prl`) and
auto-backups are intentionally git-ignored.

## Start with the wiring PDFs

If you only read one thing, read [`wiring/`](wiring): `Main_PCB.pdf`, `Power_PCB.pdf`,
`IR_PCB.pdf`, and `Line_PCB.pdf` list every connection (rails, sensor pins, UART
links) in plain language. They are the reference the firmware pin maps were verified
against.

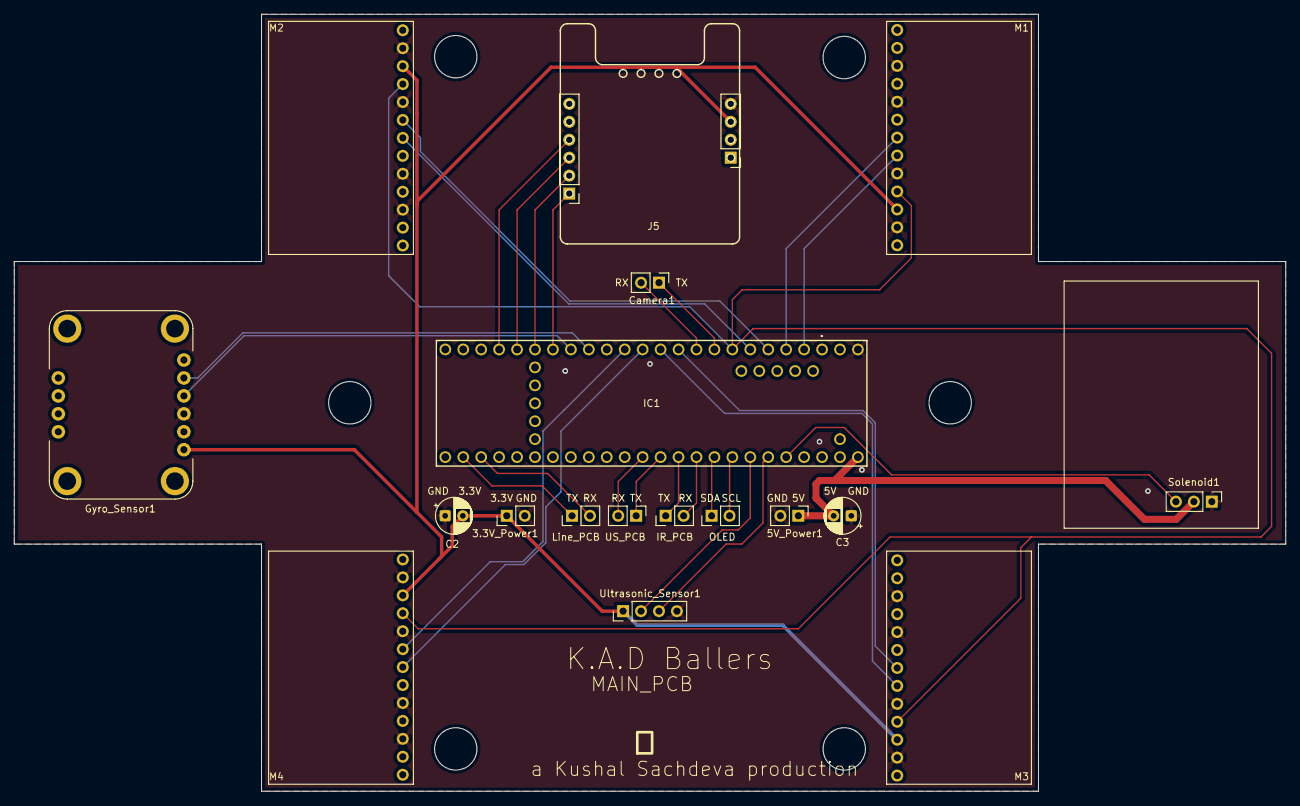
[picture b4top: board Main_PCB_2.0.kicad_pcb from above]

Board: 2 copper layers, 180.0 x 110.0 mm, 19 parts (0 on the bottom side), 31 nets.

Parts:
3.3V_Power1, 5V_Power1: Conn_01x02; PinHeader_1x02_P2.54mm_Vertical
C2, C3: 104; CP_Radial_D5.0mm_P2.50mm
Camera1: Conn_01x02; PinHeader_1x02_P2.54mm_Vertical
Gyro_Sensor1: BNO055; MODULE_2472
IC1: TEENSY_4.1; TEENSY41
IR_PCB: Conn_01x02; PinHeader_1x02_P2.54mm_Vertical
J1, J2, J3, J4: Conn_01x13; PinHeader_1x13_P2.54mm_Vertical
J5: Conn_01x06; PinHeader_1x06_P2.54mm_Vertical
J6: Conn_01x04; PinHeader_1x04_P2.54mm_Vertical
Line_PCB: Conn_01x02; PinHeader_1x02_P2.54mm_Vertical
OLED: Conn_01x02; PinHeader_1x02_P2.54mm_Vertical
Solenoid1: Conn_01x03; PinHeader_1x03_P2.54mm_Vertical
US_PCB: Conn_01x02; PinHeader_1x02_P2.54mm_Vertical
Ultrasonic_Sensor1: Conn_01x04; PinHeader_1x04_P2.54mm_Vertical

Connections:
1_IN1: IC1.2 (OUT2), J1.6
1_IN2: IC1.3 (LRCLK2), J1.7
2_IN1: IC1.4 (BCLK2), J2.6
2_IN2: IC1.5 (IN2), J2.7
3_IN1: IC1.10 (CS_1), J3.6
3_IN2: IC1.9 (OUT1C), J3.7
4_IN1: IC1.12 (MISO), J4.6
4_IN2: IC1.11 (MOSI), J4.7
+3.3V: 3.3V_Power1.1, C2.2, Gyro_Sensor1.1 (VIN), J1.3, J2.3, J3.3, J4.3, J6.3, Ultrasonic_Sensor1.1
+5V: 5V_Power1.1, C3.2, IC1.55 (VIN_(3.6_TO_5.5_VOLTS)), Solenoid1.2
Echo: IC1.21 (A7), Ultrasonic_Sensor1.3
GND: 3.3V_Power1.2, 5V_Power1.2, C2.1, C3.1, Gyro_Sensor1.3 (GND), IC1.71 (GND_6), J1.2, J1.5, J1.9, J1.11, J2.2, J2.5, J2.9, J2.11, J3.2, J3.5, J3.9, J3.11, J4.2, J4.5, J4.9, J4.11, J6.4, Solenoid1.1, Ultrasonic_Sensor1.4
IN1: IC1.22 (A8), Solenoid1.3
OUT1: IC1.26 (A12), J5.1
OUT2: IC1.27 (A13), J5.2
RX_C: Camera1.2, IC1.8 (TX2)
RX_IR: IC1.17 (A3), IR_PCB.2
RX_L: IC1.35 (TX8), Line_PCB.2
RX_M: IC1.29 (TX7), J5.4
RX_U: IC1.14 (A0), US_PCB.2
SCL_G: Gyro_Sensor1.5 (SCL), IC1.24 (A10)
SCL_S: IC1.19 (A5), OLED.2
SDA_G: Gyro_Sensor1.4 (SDA), IC1.25 (A11)
SDA_S: IC1.18 (A4), OLED.1
SLEEP: IC1.6 (OUT1D), J1.4, J2.4, J3.4, J4.4
TX_C: Camera1.1, IC1.7 (RX2)
TX_IR: IC1.16 (A2), IR_PCB.1
TX_L: IC1.34 (RX8), Line_PCB.1
TX_M: IC1.28 (RX7), J5.3
TX_U: IC1.15 (A1), US_PCB.1
Trig: IC1.20 (A6), Ultrasonic_Sensor1.2

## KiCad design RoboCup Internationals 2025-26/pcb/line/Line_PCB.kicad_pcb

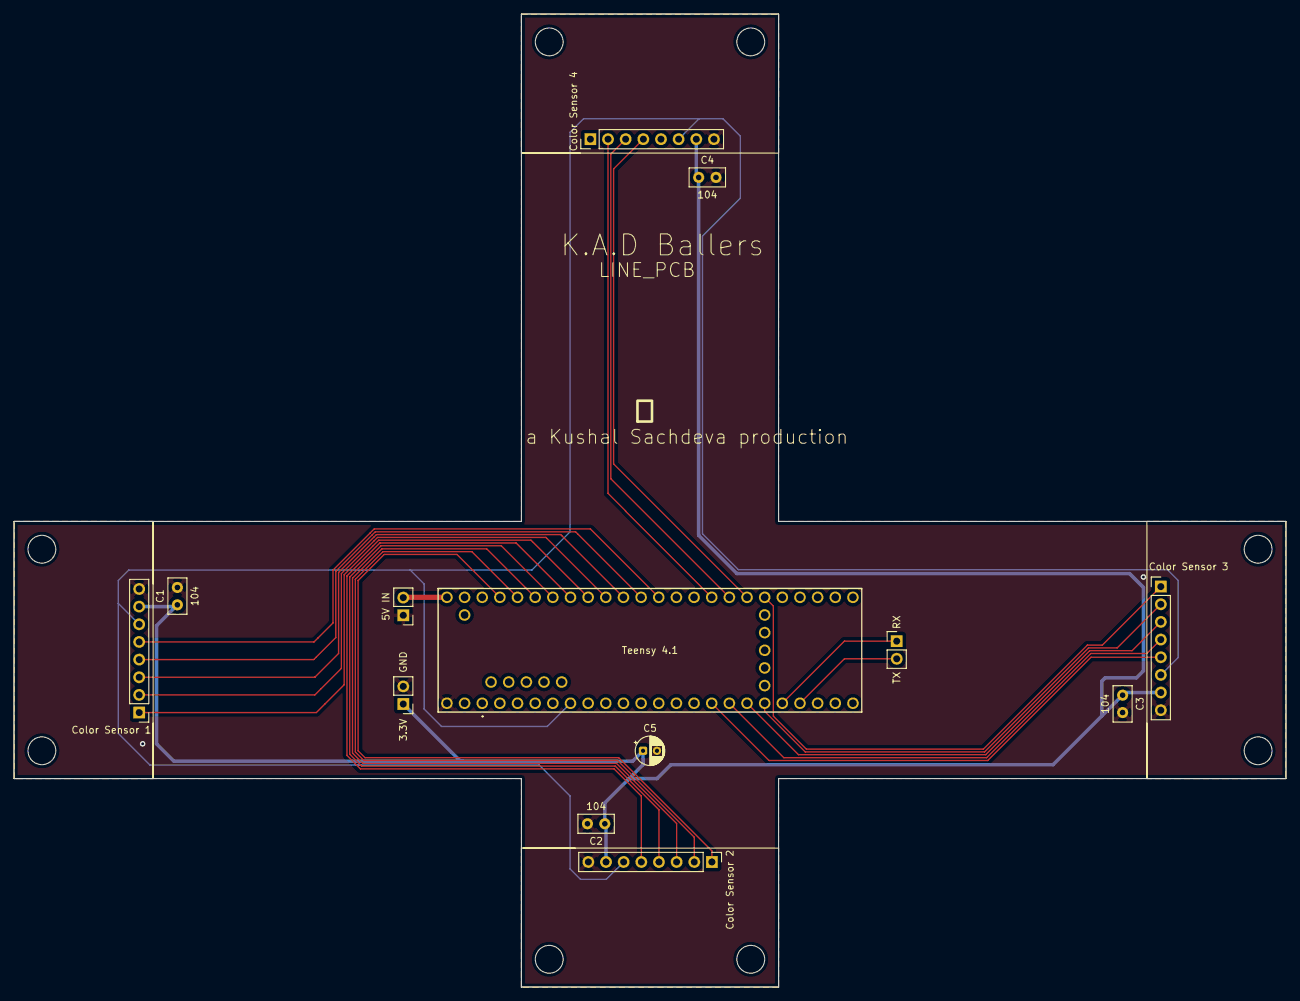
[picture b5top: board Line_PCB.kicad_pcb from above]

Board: 2 copper layers, 183.0 x 140.0 mm, 13 parts (0 on the bottom side), 24 nets.

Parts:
5V IN: Conn_01x02; PinHeader_1x02_P2.54mm_Vertical
C1, C2, C3, C4: 104; C_Disc_D5.0mm_W2.5mm_P2.50mm
C5: 104; CP_Radial_D4.0mm_P2.00mm
Color Sensor 1, Color Sensor 2, Color Sensor 3, Color Sensor 4: Conn_01x08; PinHeader_1x08_P2.54mm_Vertical
J5, J6: Conn_01x02; PinHeader_1x02_P2.54mm_Vertical
Teensy 4.1: TEENSY_4.1; TEENSY41

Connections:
+3.3V: C1.1, C2.1, C3.1, C4.1, C5.1, Color Sensor 1.7, Color Sensor 2.7, Color Sensor 3.7, Color Sensor 4.7, J5.1
+5V: 5V IN.2, Teensy 4.1.55 (VIN_(3.6_TO_5.5_VOLTS))
GND: 5V IN.1, C1.2, C2.2, C3.2, C4.2, C5.2, Color Sensor 1.8, Color Sensor 2.8, Color Sensor 3.8, Color Sensor 4.8, J5.2, Teensy 4.1.71 (GND_6)
Odd: Color Sensor 1.6, Color Sensor 2.6, Color Sensor 3.6, Color Sensor 4.6, Teensy 4.1.6 (OUT1D)
Out1: Color Sensor 1.5, Teensy 4.1.14 (A0)
Out2: Color Sensor 1.4, Teensy 4.1.15 (A1)
Out3: Color Sensor 1.3, Teensy 4.1.16 (A2)
Out4: Color Sensor 1.2, Teensy 4.1.17 (A3)
Out5: Color Sensor 1.1, Teensy 4.1.18 (A4)
Out6: Color Sensor 2.5, Teensy 4.1.19 (A5)
Out7: Color Sensor 2.4, Teensy 4.1.20 (A6)
Out8: Color Sensor 2.3, Teensy 4.1.21 (A7)
Out9: Color Sensor 2.2, Teensy 4.1.22 (A8)
Out10: Color Sensor 2.1, Teensy 4.1.23 (A9)
Out11: Color Sensor 3.5, Teensy 4.1.24 (A10)
Out12: Color Sensor 3.4, Teensy 4.1.25 (A11)
Out13: Color Sensor 3.3, Teensy 4.1.26 (A12)
Out14: Color Sensor 3.2, Teensy 4.1.27 (A13)
Out15: Color Sensor 3.1, Teensy 4.1.38 (A14)
Out16: Color Sensor 4.4, Teensy 4.1.39 (A15)
Out17: Color Sensor 4.3, Teensy 4.1.40 (A16)
Out18: Color Sensor 4.2, Teensy 4.1.41 (A17)
RX_Out: J6.1, Teensy 4.1.28 (RX7)
TX_Out: J6.2, Teensy 4.1.29 (TX7)

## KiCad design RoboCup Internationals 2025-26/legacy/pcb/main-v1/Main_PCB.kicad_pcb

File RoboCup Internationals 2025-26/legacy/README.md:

# Legacy / archive

Superseded designs, kept for history and reference. **Nothing here is the current
build** — see the top-level `firmware/`, `pcb/`, and `cad/` for what the robot
actually runs and uses today.

## What's here and why it was replaced

### `firmware/attacker/`
- **`attacker_chase_aim_kick`** — the attacker *before* the line ring was added. It
  flees walls on **ultrasonic alone**. Superseded by
  `firmware/attacker/attacker_chase_aim_kick_line`, which only flees when the line
  ring **and** ultrasonics agree (far fewer false escapes; safer against the
  out-of-bounds penalty).
- **`ir_ball_chase_avoid_angle`** — the original foundation sketch: IR chase +
  ultrasonic avoidance + heading hold + **HC-05 Bluetooth telemetry**, no camera. The
  current attacker grew out of this; kept because its comments document the drive
  base and parsers it all started from.

### `firmware/defender/`
- **`Defender_NoLine`** — a simple bang-bang goalkeeper using **ultrasonics only**
  (back-wall standoff band + side-wall avoidance + IR left/right tracking), no line
  ring and no state machine. A dependable fallback; superseded by `Defender_Full`,
  which uses the line ring as the primary box reference.

### `pcb/main-v1/`
- The **first main-board revision** (`Main_PCB`), replaced by `pcb/main`
  (`Main_PCB 2.0`).

### `cad/`
- **`old-models/`** and **`not-using/`** — earlier chassis, motor-bracket, and
  support-beam studies that were iterated past.

> These were **archived rather than deleted** so the design history — and the
> "why we changed it" — stays available.

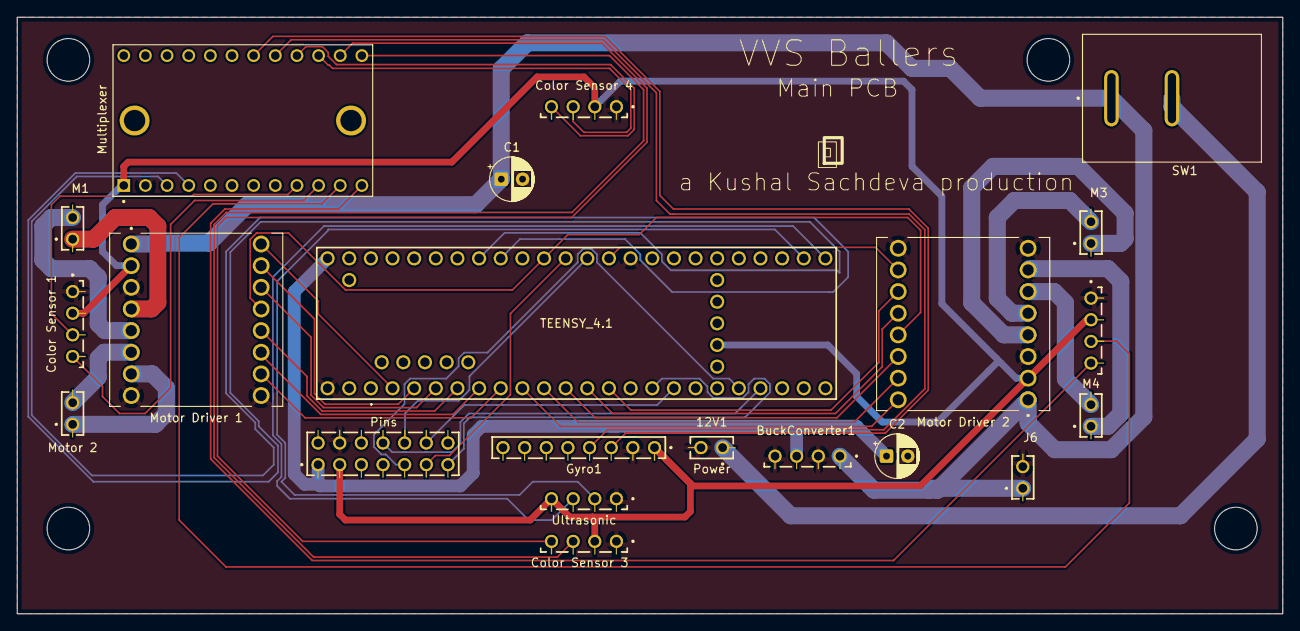
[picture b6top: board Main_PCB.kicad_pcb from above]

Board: 2 copper layers, 148.5 x 70.0 mm, 21 parts (0 on the bottom side), 46 nets.

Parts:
12V1: Power; SAMTEC_MTLW-101-06-S-D-105
BuckConverter1: 12V to 5V; SAMTEC_MTLW-104-X-X-S-X
C1, C2: C; CP_Radial_D5.0mm_P2.50mm
Gyro1: Gyro; SAMTEC_MTLW-108-07-S-S-250
IC1: TEENSY_4.1; TEENSY41
J1: Color Sensor 1; SAMTEC_MTLW-104-X-X-S-X
J2: Color Sensor 2; SAMTEC_MTLW-104-X-X-S-X
J3: Color Sensor 3; SAMTEC_MTLW-104-X-X-S-X
J4: Color Sensor 4; SAMTEC_MTLW-104-X-X-S-X
J5: Ultrasonic; SAMTEC_MTLW-104-X-X-S-X
J6: Kicker; SAMTEC_MTLW-101-06-S-D-105
M1: Motor 1; SAMTEC_MTLW-101-06-S-D-105
M2: Motor 2; SAMTEC_MTLW-101-06-S-D-105
M3: Motor 3; SAMTEC_MTLW-101-06-S-D-105
M4: Motor 4; SAMTEC_MTLW-101-06-S-D-105
Motor Driver 1, Motor Driver 2: ROB-14450; MODULE_ROB-14450
Multiplexer: 2717; MODULE_2717
Pins: IR PCB; SAMTEC_MTLW-107-XX-X-D-XXX
SW1: SW_DIP_x01; SW_RF1-1A-DC-2-R-1

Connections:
GND: 12V1.02 (GND), BuckConverter1.02 (GND_IN), BuckConverter1.04 (GND_OUT), C1.2, C2.2, Gyro1.02 (GND), IC1.69 (GND_4), IC1.71 (GND_6), J1.01 (GND), J2.01 (GND), J3.01 (GND), J4.01 (GND), J5.01 (GND), J6.02 (GND), Motor Driver 1.3 (GND), Motor Driver 1.8 (GND), Motor Driver 1.9 (GND), Motor Driver 2.3 (GND), Motor Driver 2.8 (GND), Motor Driver 2.9 (GND), Multiplexer.2 (GND), Pins.04 (GND)
unnamed: 12V1.01 (12V), SW1.2
unnamed: BuckConverter1.03 (5V_OUT), C2.1, IC1.55 (VIN_(3.6_TO_5.5_VOLTS)), Pins.01 (5V)
unnamed: BuckConverter1.01 (12V_IN), C1.1, J6.01 (12V), Motor Driver 1.1 (VM), Motor Driver 2.1 (VM), SW1.1
unnamed: Gyro1.03 (SCL), Multiplexer.18 (SCL4)
unnamed: Gyro1.04 (SDA), Multiplexer.17 (SDA4)
unnamed: Gyro1.01 (VCC), IC1.44 (3.3V_2), J1.02 (VCC), J2.02 (VCC), J3.02 (VCC), J4.02 (VCC), J5.04 (Vcc), Motor Driver 1.2 (VCC), Motor Driver 2.2 (VCC), Multiplexer.1 (VIN), Pins.03 (3.3V)
unnamed: IC1.14 (A0), Pins.10 (RX_IR)
unnamed: IC1.15 (A1), Pins.11 (TX_IR)
unnamed: IC1.16 (A2), Motor Driver 1.13 (STBY), Motor Driver 2.13 (STBY)
unnamed: IC1.18 (A4), Multiplexer.3 (SDA)
unnamed: IC1.19 (A5), Multiplexer.4 (SCL)
unnamed: IC1.24 (A10), Pins.13 (SCL)
unnamed: IC1.25 (A11), Pins.12 (SDA)
unnamed: IC1.4 (BCLK2), Motor Driver 1.14 (AI1)
unnamed: IC1.10 (CS_1), Motor Driver 2.14 (AI1)
unnamed: IC1.5 (IN2), Motor Driver 1.12 (BI1)
unnamed: IC1.3 (LRCLK2), Motor Driver 1.15 (AI2)
unnamed: IC1.33 (MCLK2), J5.03 (Trig)
unnamed: IC1.12 (MISO), Motor Driver 2.11 (BI2)
unnamed: IC1.11 (MOSI), Motor Driver 2.12 (BI1)
unnamed: IC1.9 (OUT1C), Motor Driver 2.15 (AI2)
unnamed: IC1.6 (OUT1D), Motor Driver 1.11 (BI2)
unnamed: IC1.2 (OUT2), Motor Driver 1.16 (PWMA)
unnamed: IC1.7 (RX2), Motor Driver 1.10 (PWMB)
unnamed: IC1.28 (RX7), Pins.09 (TX_C)
unnamed: IC1.34 (RX8), J5.02 (Echo)
unnamed: IC1.13 (SCK), Motor Driver 2.10 (PWMB)
unnamed: IC1.8 (TX2), Motor Driver 2.16 (PWMA)
unnamed: IC1.29 (TX7), Pins.08 (RX_C)
unnamed: J1.04 (SCL), Multiplexer.10 (SCL0)
unnamed: J1.03 (SDA), Multiplexer.9 (SDA0)
unnamed: J2.04 (SCL), Multiplexer.12 (SCL1)
unnamed: J2.03 (SDA), Multiplexer.11 (SDA1)
unnamed: J3.04 (SCL), Multiplexer.14 (SCL2)
unnamed: J3.03 (SDA), Multiplexer.13 (SDA2)
unnamed: J4.04 (SCL), Multiplexer.16 (SCL3)
unnamed: J4.03 (SDA), Multiplexer.15 (SDA3)
unnamed: M1.01, Motor Driver 1.4 (A01)
unnamed: M1.02, Motor Driver 1.5 (A02)
unnamed: M2.01, Motor Driver 1.7 (B01)
unnamed: M2.02, Motor Driver 1.6 (B02)
unnamed: M3.01, Motor Driver 2.4 (A01)
unnamed: M3.02, Motor Driver 2.5 (A02)
unnamed: M4.01, Motor Driver 2.7 (B01)
unnamed: M4.02, Motor Driver 2.6 (B02)
